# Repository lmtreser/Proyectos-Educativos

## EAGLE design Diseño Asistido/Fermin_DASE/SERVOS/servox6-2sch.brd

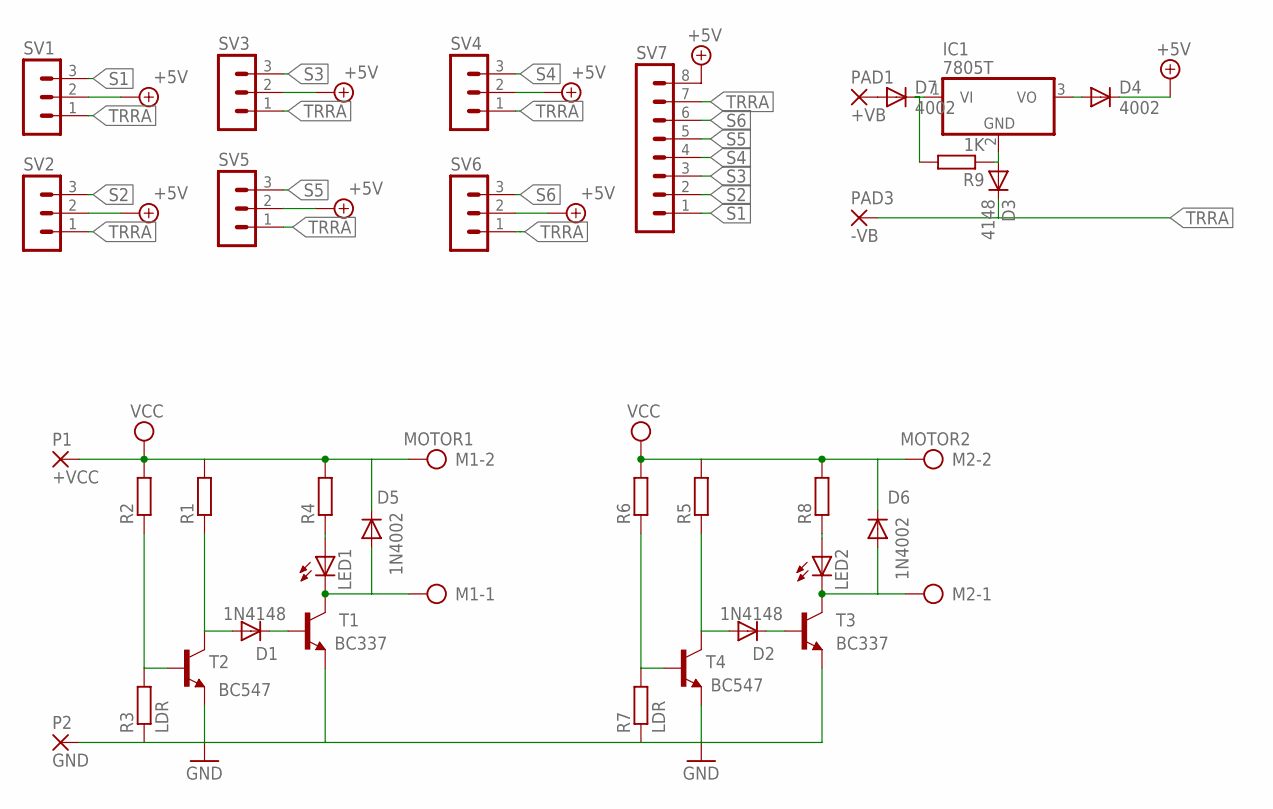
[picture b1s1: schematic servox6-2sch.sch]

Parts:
D1, D2: 1N4148; DO35-7
D3: 4148; DO35-7
D4, D7: 4002; DO35-7
D5, D6: 1N4002; DO41-10
IC1: 7805T; TO220H
LED1, LED2: LED3MM
M1: MOTOR1; AK500/2
M2: MOTOR2; AK500/2
P1: +VCC; 2,15/1,0
P2: GND; 2,15/1,0
PAD1: +VB; 1,6/0,9
PAD3: -VB; 1,6/0,9
R1, R2, R4, R5, R6, R8: R-EU_0207/7; 0207/7
R3, R7: LDR; 0204/5
R9: 1K; 0207/7
SV1, SV2, SV3, SV4, SV5, SV6: MA03-1
SV7: MA08-1
T1, T3: BC337; TO92-CBE
T2, T4: BC547; TO92-CBE

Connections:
+5V: D4.C, SV1.2, SV2.2, SV3.2, SV4.2, SV5.2, SV6.2, SV7.8
GND: P2.1, R3.1, R7.1, T1.E, T2.E, T3.E, T4.E
unnamed: D1.C, T1.B
unnamed: D1.A, R1.1, T2.C
unnamed: D5.A, LED1.K (C), M1.1, T1.C
unnamed: D3.A, IC1.2 (GND), R9.1
unnamed: LED1.A, R4.1
unnamed: R2.1, R3.2, T2.B
unnamed: D2.C, T3.B
unnamed: D2.A, R5.1, T4.C
unnamed: D6.A, LED2.K (C), M2.1, T3.C
unnamed: D4.A, IC1.3 (VO)
unnamed: R6.1, R7.2, T4.B
unnamed: LED2.A, R8.1
unnamed: D7.C, IC1.1 (VI), R9.2
unnamed: D7.A, PAD1.1
S1: SV1.3, SV7.1
S2: SV2.3, SV7.2
S3: SV3.3, SV7.3
S4: SV4.3, SV7.4
S5: SV5.3, SV7.5
S6: SV6.3, SV7.6
TRRA: D3.C, PAD3.1, SV1.1, SV2.1, SV3.1, SV4.1, SV5.1, SV6.1, SV7.7
VCC: D5.C, D6.C, M1.2, M2.2, P1.1, R1.2, R2.2, R4.2, R5.2, R6.2, R8.2

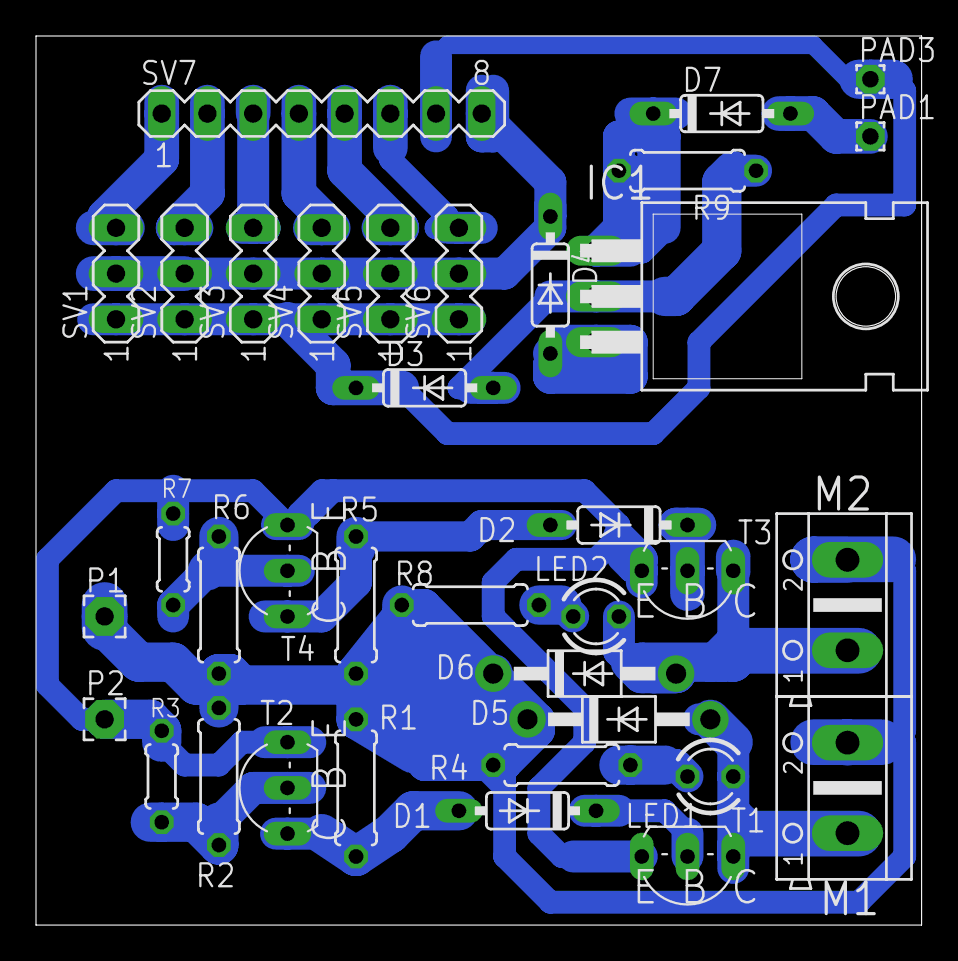
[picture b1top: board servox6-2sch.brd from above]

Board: 2 copper layers, 49.2 x 49.4 mm, 36 parts (0 on the bottom side), 24 nets.

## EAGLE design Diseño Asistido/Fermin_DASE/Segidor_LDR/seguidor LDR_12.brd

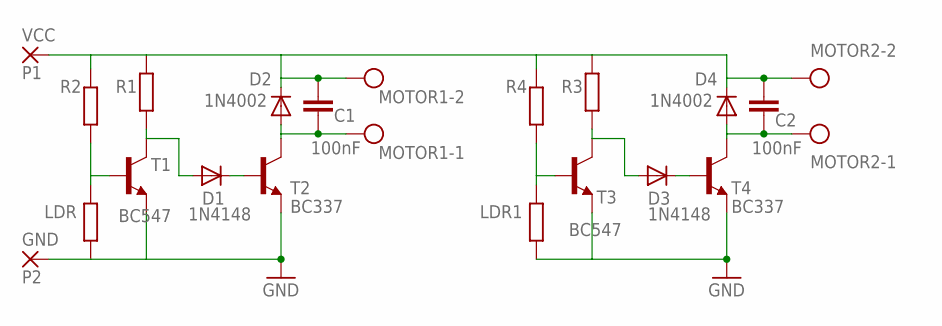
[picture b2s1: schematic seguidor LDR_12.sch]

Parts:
C1, C2: 100nF; C050-025X075
D1, D3: 1N4148; DO35-10
D2, D4: 1N4002; DO41-10
GND: P2; 2,15/1,0
LDR, LDR1: R-EU_0204/5; 0204/5
MOTOR1, MOTOR2: AK500/2
R1, R2, R3, R4: R-EU_0207/10; 0207/10
T1, T3: BC547; TO92-CBE
T2, T4: BC337; TO92-CBE
VCC: P1; 2,15/1,0

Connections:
GND: GND.1, LDR.1, LDR1.1, T1.E, T2.E, T3.E, T4.E
unnamed: LDR.2, R2.1, T1.B
unnamed: LDR1.2, R4.1, T3.B
unnamed: C1.1, C2.1, D2.C, D4.C, MOTOR1.2, MOTOR2.2, R1.2, R2.2, R3.2, R4.2, VCC.1
unnamed: D3.A, R3.1, T3.C
unnamed: D1.A, R1.1, T1.C
unnamed: D1.C, T2.B
unnamed: C1.2, D2.A, MOTOR1.1, T2.C
unnamed: D3.C, T4.B
unnamed: C2.2, D4.A, MOTOR2.1, T4.C

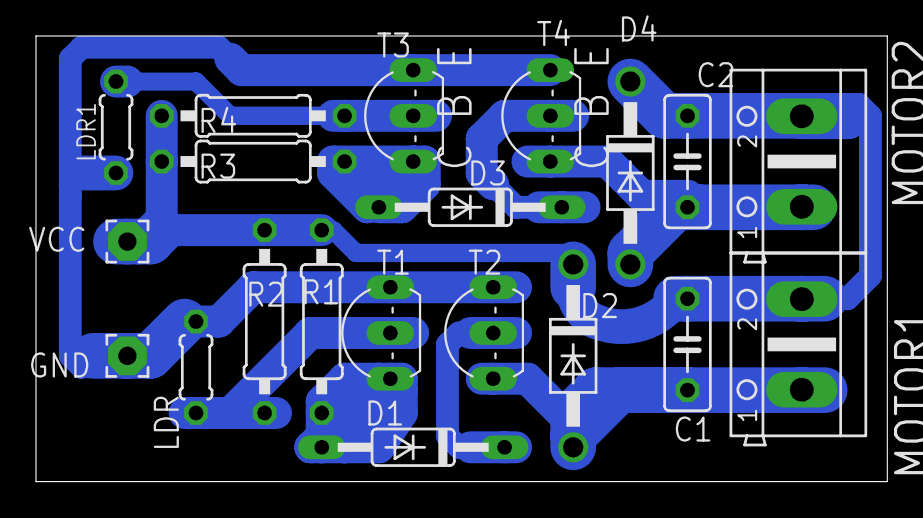
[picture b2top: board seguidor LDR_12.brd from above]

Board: 2 copper layers, 47.3 x 24.8 mm, 20 parts (0 on the bottom side), 10 nets.

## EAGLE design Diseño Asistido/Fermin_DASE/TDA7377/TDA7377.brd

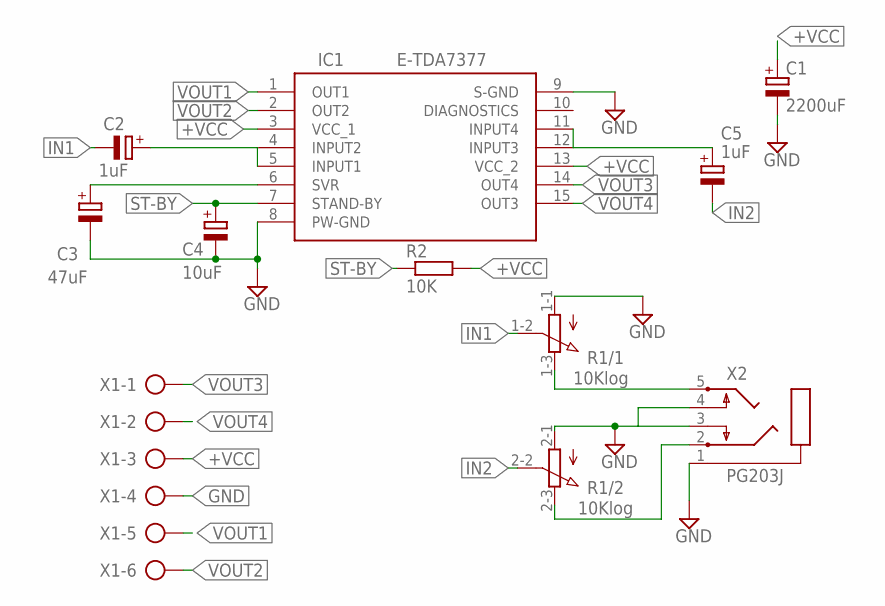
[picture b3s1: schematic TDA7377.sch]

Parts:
C1: 2200uF; E5-13
C2: 1uF; E2,5-6
C3: 47uF; E2,5-6
C4: 10uF; E2,5-5
C5: 1uF; E5-5
IC1: E-TDA7377; TO127P500X2020X2210-15P
R1: 10Klog; 3RP/1610G
R2: 10K; 0207/10
X1: AK500/6-H
X2: PG203J

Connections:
+VCC: C1.+, IC1.3 (VCC_1), IC1.13 (VCC_2), R2.2, X1.3
GND: C1.-, C3.-, C4.-, IC1.8 (PW-GND), IC1.9 (S-GND), R1.1-1 (A), R1.2-1 (A), X1.4, X2.1, X2.3, X2.4
IN1: C2.-, R1.1-2 (S)
IN2: C5.-, R1.2-2 (S)
unnamed: C2.+, IC1.4 (INPUT2), IC1.5 (INPUT1)
unnamed: C3.+, IC1.6 (SVR)
unnamed: C5.+, IC1.11 (INPUT4), IC1.12 (INPUT3)
unnamed: R1.2-3 (E), X2.2
unnamed: R1.1-3 (E), X2.5
ST-BY: C4.+, IC1.7 (STAND-BY), R2.1
VOUT1: IC1.1 (OUT1), X1.5
VOUT2: IC1.2 (OUT2), X1.6
VOUT3: IC1.14 (OUT4), X1.1
VOUT4: IC1.15 (OUT3), X1.2

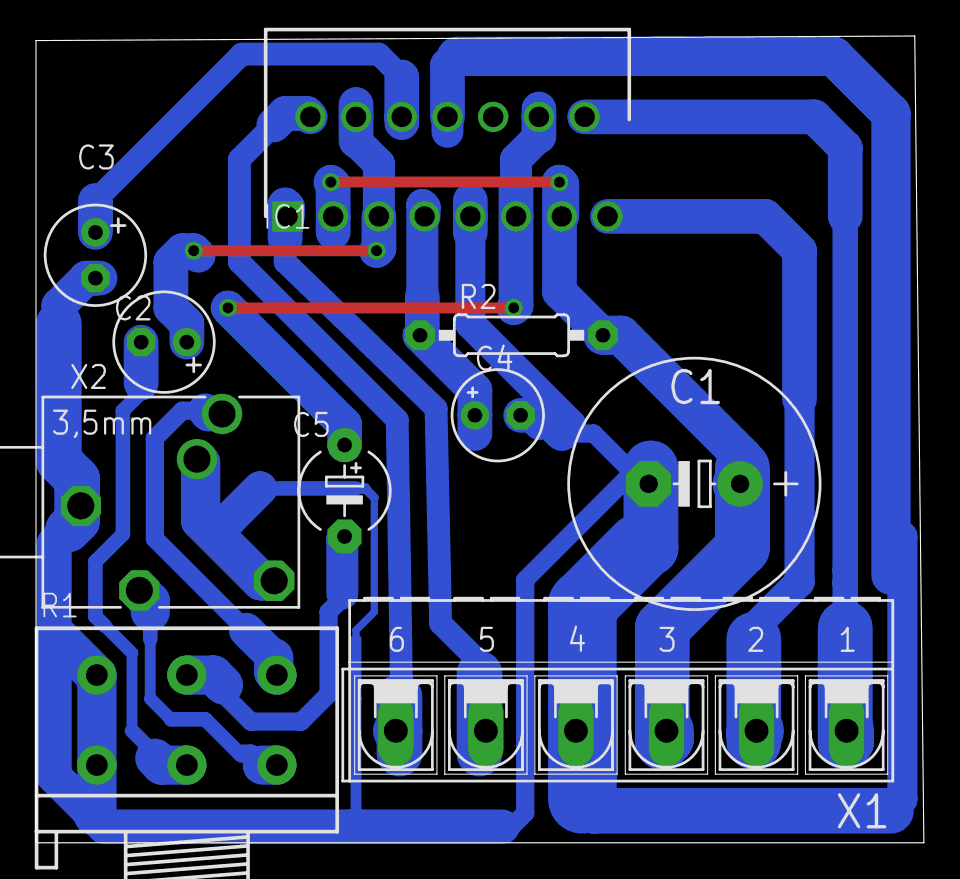
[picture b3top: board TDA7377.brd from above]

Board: 2 copper layers, 49.3 x 44.8 mm, 10 parts (0 on the bottom side), 14 nets.

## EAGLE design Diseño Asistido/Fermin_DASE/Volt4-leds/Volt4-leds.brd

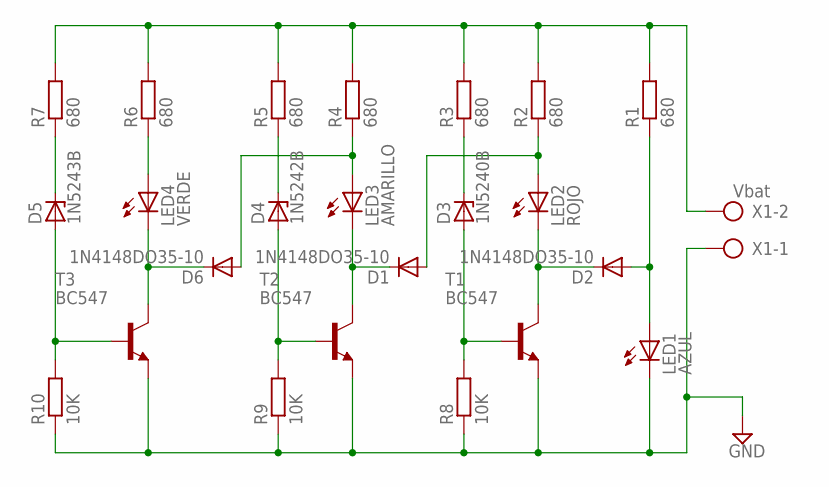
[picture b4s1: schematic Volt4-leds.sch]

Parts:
D1, D2, D6: 1N4148DO35-10; DO35-10
D3: 1N5240B; DO35Z10
D4: 1N5242B; DO35Z10
D5: 1N5243B; DO35Z10
LED1: AZUL; LED3MM
LED2: ROJO; LED3MM
LED3: AMARILLO; LED3MM
LED4: VERDE; LED3MM
R1, R2, R3, R4, R5, R6, R7: 680; 0207/10
R8, R9, R10: 10K; 0207/10
T1, T2, T3: BC547; TO92
X1: Vbat; AK500/2

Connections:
GND: LED1.K (C), R8.1, R9.1, R10.1, T1.1 (E), T2.1 (E), T3.1 (E), X1.1
unnamed: R1.2, R2.2, R3.2, R4.2, R5.2, R6.2, R7.2, X1.2
unnamed: D3.C, R3.1
unnamed: D1.A, LED2.A, R2.1
unnamed: D2.C, LED2.K (C), T1.3 (C)
unnamed: D3.A, R8.2, T1.2 (B)
unnamed: D5.A, R10.2, T3.2 (B)
unnamed: D4.A, R9.2, T2.2 (B)
unnamed: D1.C, LED3.K (C), T2.3 (C)
unnamed: D6.A, LED3.A, R4.1
unnamed: D4.C, R5.1
unnamed: D6.C, LED4.K (C), T3.3 (C)
unnamed: LED4.A, R6.1
unnamed: D5.C, R7.1
unnamed: D2.A, LED1.A, R1.1

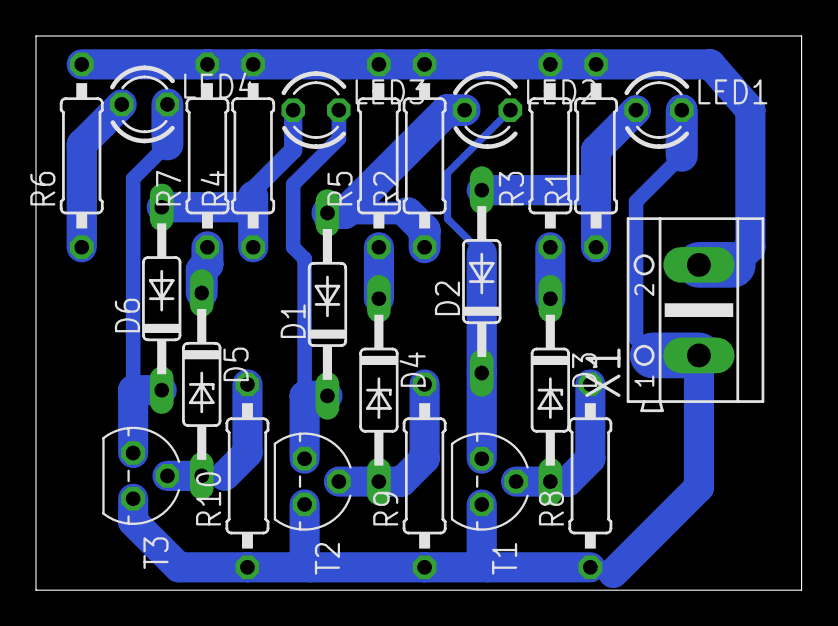
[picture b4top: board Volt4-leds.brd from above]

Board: 2 copper layers, 42.5 x 30.8 mm, 24 parts (0 on the bottom side), 15 nets.

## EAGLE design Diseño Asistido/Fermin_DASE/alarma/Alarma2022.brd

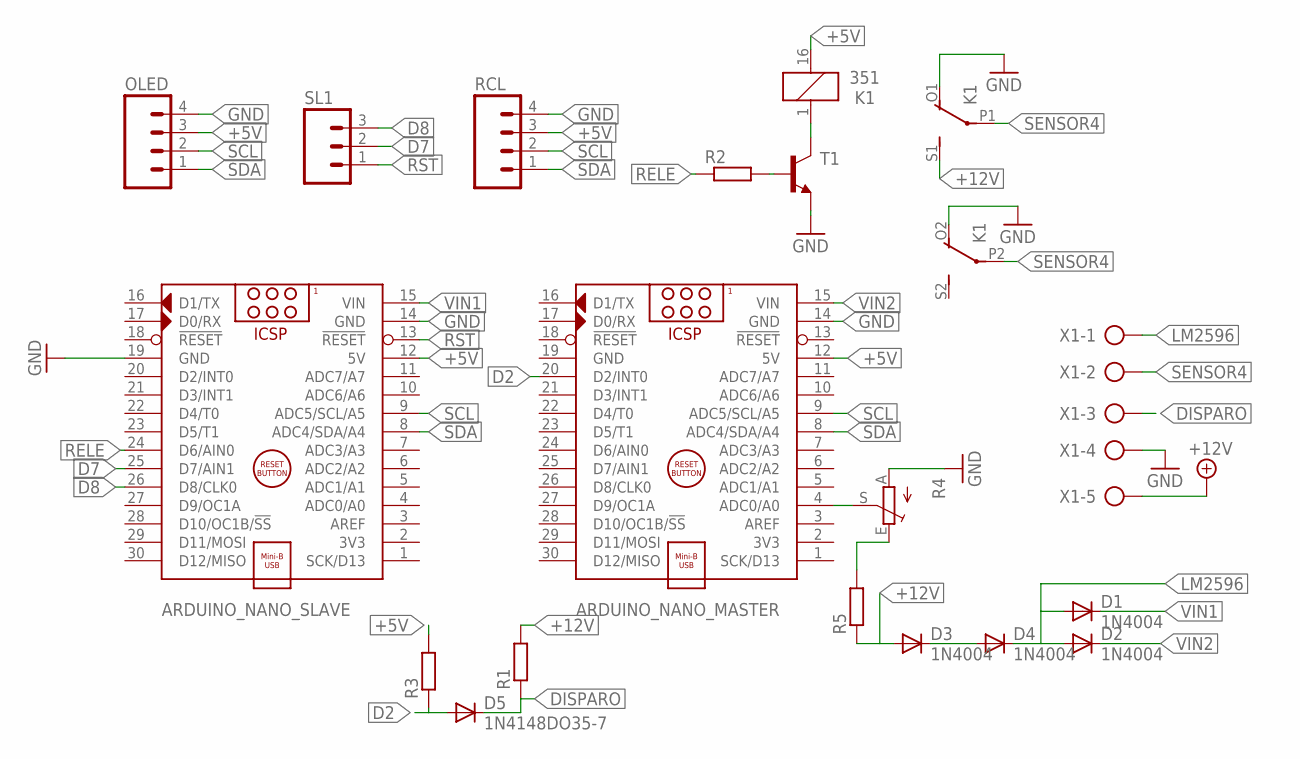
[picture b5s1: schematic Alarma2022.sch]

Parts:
ARDUINO_NANO_MASTER: ARDUINO_NANO
ARDUINO_NANO_SLAVE: ARDUINO_NANO
D1, D2, D3, D4: 1N4004; DO41-10
D5: 1N4148DO35-7; DO35-7
K1: 351
OLED: M04; 04P
R1, R2, R3: R-EU_0207/10; 0207/10
R4: TRIM_EU-B64Y; B64Y
R5: R-EU_0207/7; 0207/7
RCL: M04; 04P
SL1: M03; 03P
T1: BC337-NPN-TO92-CBE; TO92-CBE
X1: AK500/5-H

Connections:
+5V: ARDUINO_NANO_MASTER.12 (5V), ARDUINO_NANO_SLAVE.12 (5V), K1.16 (2), OLED.3, R3.2, RCL.3
+12V: D3.A, K1.S1 (S), R1.2, R5.1, X1.5
D2: ARDUINO_NANO_MASTER.20 (D2/INT0), D5.A, R3.1
D7: ARDUINO_NANO_SLAVE.25 (D7/AIN1), SL1.2
D8: ARDUINO_NANO_SLAVE.26 (D8/CLK0), SL1.3
DISPARO: D5.C, R1.1, X1.3
GND: ARDUINO_NANO_MASTER.14 (GND), ARDUINO_NANO_MASTER.19 (GND), ARDUINO_NANO_SLAVE.14 (GND), ARDUINO_NANO_SLAVE.19 (GND), K1.O1 (O), K1.O2 (O), OLED.4, R4.A, RCL.4, T1.E, X1.4
LM2596: D1.A, D2.A, D4.C, X1.1
unnamed: K1.1, T1.C
unnamed: R2.2, T1.B
unnamed: ARDUINO_NANO_MASTER.4 (ADC0/A0), R4.S
unnamed: R4.E, R5.2
unnamed: D3.C, D4.A
RELE: ARDUINO_NANO_SLAVE.24 (D6/AIN0), R2.1
RST: ARDUINO_NANO_SLAVE.13 (!RESET), SL1.1
SCL: ARDUINO_NANO_MASTER.9 (ADC5/SCL/A5), ARDUINO_NANO_SLAVE.9 (ADC5/SCL/A5), OLED.2, RCL.2
SDA: ARDUINO_NANO_MASTER.8 (ADC4/SDA/A4), ARDUINO_NANO_SLAVE.8 (ADC4/SDA/A4), OLED.1, RCL.1
SENSOR4: K1.P1, K1.P2, X1.2
VIN1: ARDUINO_NANO_SLAVE.15 (VIN), D1.C
VIN2: ARDUINO_NANO_MASTER.15 (VIN), D2.C

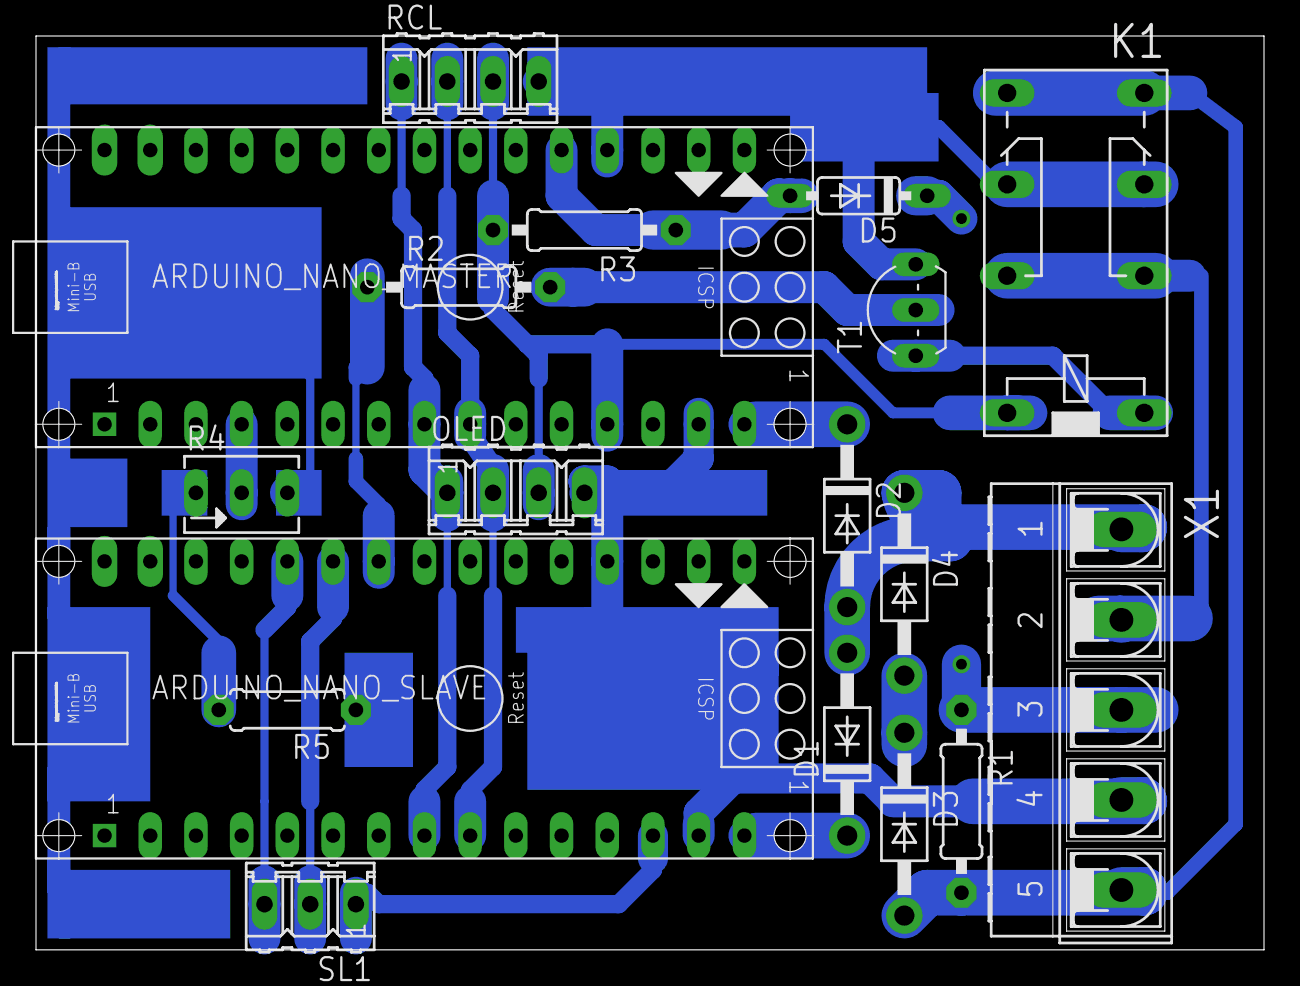
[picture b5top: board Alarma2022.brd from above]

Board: 2 copper layers, 68.2 x 50.8 mm, 18 parts (0 on the bottom side), 20 nets.

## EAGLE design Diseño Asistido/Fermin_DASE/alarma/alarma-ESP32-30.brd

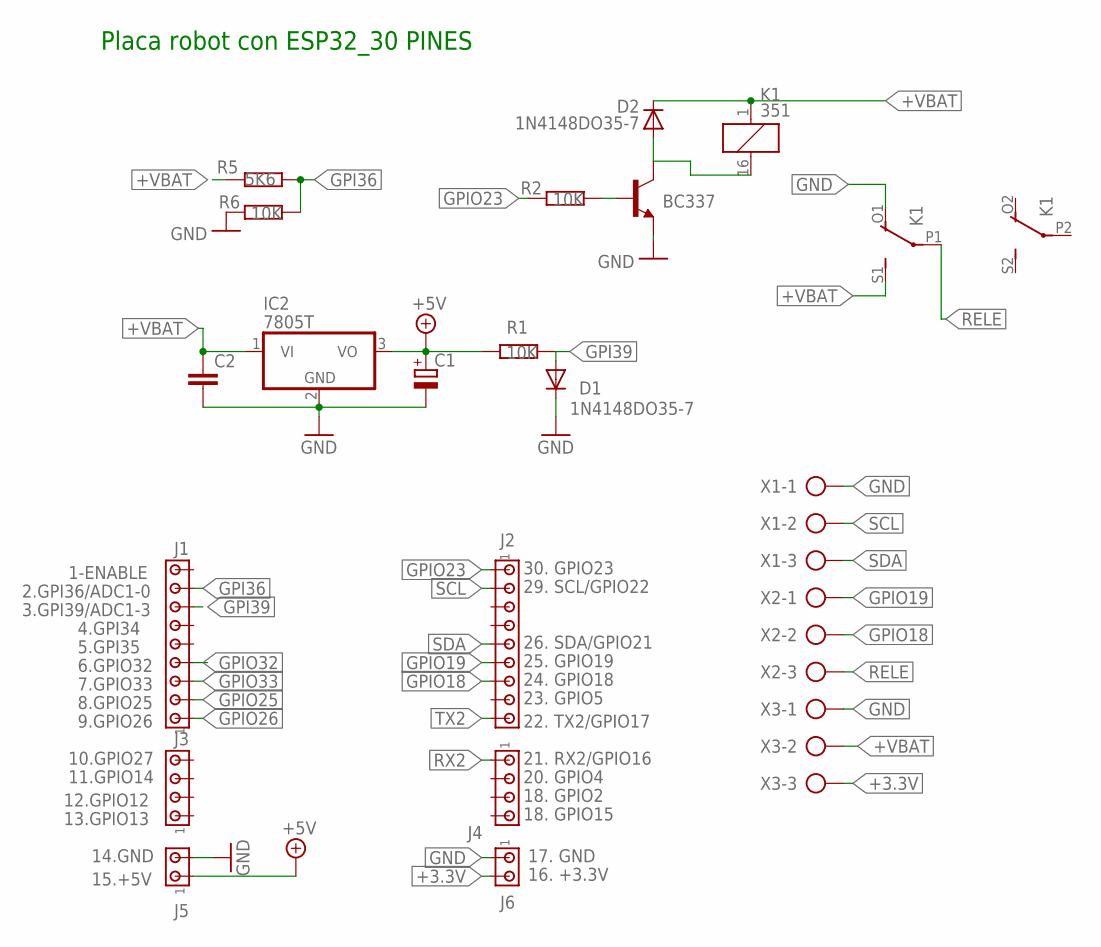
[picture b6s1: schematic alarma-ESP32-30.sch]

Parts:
BC337: BC337-16-NPN-TO92-CBE; TO92-CBE
C1: CPOL-EUE2.5-6; E2,5-6
C2: C-EU025-025X050; C025-025X050
D1, D2: 1N4148DO35-7; DO35-7
IC2: 7805T; TO220H
J1, J2: MTA09-100; 10X09MTA
J3, J4: MTA04-100; 10X04MTA
J5, J6: MTA02-100; 10X02MTA
K1: 351
R1, R6: 10K; 0207/7
R2: 10K; 0207/15
R5: 5K6; 0207/7
X1, X2, X3: AK500/3

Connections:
+3.3V: J6.2, X3.3
+5V: C1.+, IC2.3 (VO), J5.1, R1.2
+VBAT: C2.1, D2.C, IC2.1 (VI), K1.1, K1.S1 (S), R5.1, X3.2
GND: BC337.E, C1.-, C2.2, D1.C, IC2.2 (GND), J5.2, J6.1, K1.O1 (O), R6.2, X1.1, X3.1
GPI36: J1.8, R5.2, R6.1
GPI39: D1.A, J1.7, R1.1
GPIO18: J2.7, X2.2
GPIO19: J2.6, X2.1
GPIO23: J2.1, R2.2
GPIO25: J1.2
GPIO26: J1.1
GPIO32: J1.4
GPIO33: J1.3
unnamed: BC337.C, D2.A, K1.16 (2)
unnamed: BC337.B, R2.1
RELE: K1.P1, X2.3
RX2: J4.1
SCL: J2.2, X1.2
SDA: J2.5, X1.3
TX2: J2.9

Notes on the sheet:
16. +3.3V
1-ENABLE
2.GPI36/ADC1-0
3.GPI39/ADC1-3
4.GPI34
5.GPI35
6.GPIO32
7.GPIO33
8.GPIO25
9.GPIO26
10.GPIO27
11.GPIO14
13.GPIO13
15.+5V
30. GPIO23
29. SCL/GPIO22
26. SDA/GPIO21
14.GND
25. GPIO19
24. GPIO18
22. TX2/GPIO17
21. RX2/GPIO16
20. GPIO4
Placa robot con ESP32_30 PINES
12.GPIO12
17. GND
18. GPIO15
18. GPIO2
23. GPIO5

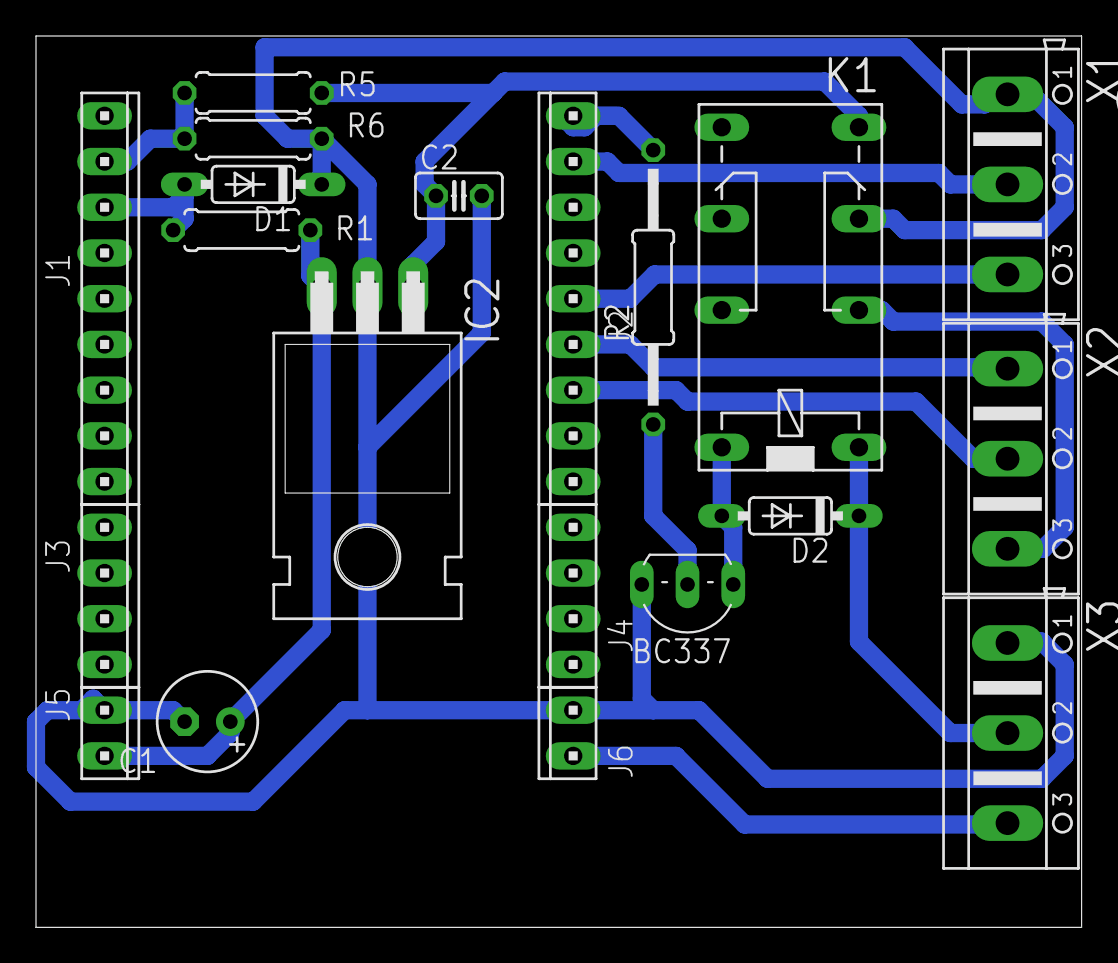
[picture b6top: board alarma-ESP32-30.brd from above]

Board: 2 copper layers, 58.1 x 49.5 mm, 20 parts (0 on the bottom side), 14 nets.

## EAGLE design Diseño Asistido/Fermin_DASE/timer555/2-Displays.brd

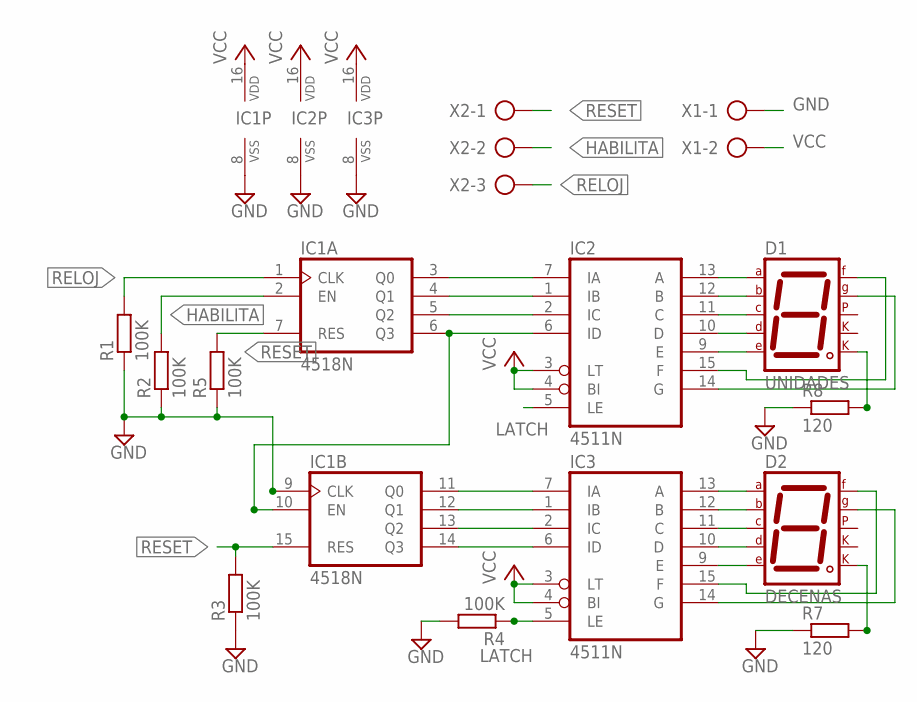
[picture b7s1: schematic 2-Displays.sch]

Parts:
D1: UNIDADES; 7SEG-13
D2: DECENAS; 7SEG-13
IC1: 4518N; DIL16
IC2, IC3: 4511N; DIL16
R1, R2, R3, R4, R5: 100K; 0207/7
R7, R8: 120; 0207/7
X1: AK500/2-H
X2: AK500/3-H

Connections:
GND: IC1.8 (VSS), IC1.9 (CLK), IC2.8 (VSS), IC3.8 (VSS), R1.1, R2.1, R3.1, R4.2, R5.1, R7.1, R8.1, X1.1
HABILITA: IC1.2 (EN), R2.2, X2.2
LATCH: IC2.5 (LE), IC3.5 (LE), R4.1
unnamed: IC1.3 (Q0), IC2.7 (IA)
unnamed: IC1.4 (Q1), IC2.1 (IB)
unnamed: IC1.5 (Q2), IC2.2 (IC)
unnamed: D1.8 (CK2), R8.2
unnamed: D2.7 (A), IC3.13 (A)
unnamed: D2.6 (B), IC3.12 (B)
unnamed: D2.4 (C), IC3.11 (C)
unnamed: D2.2 (D), IC3.10 (D)
unnamed: D2.1 (E), IC3.9 (E)
unnamed: IC1.11 (Q0), IC3.7 (IA)
unnamed: IC1.12 (Q1), IC3.1 (IB)
unnamed: IC1.14 (Q3), IC3.6 (ID)
unnamed: IC1.13 (Q2), IC3.2 (IC)
unnamed: D2.9 (F), IC3.15 (F)
unnamed: D2.10 (G), IC3.14 (G)
unnamed: D2.8 (CK2), R7.2
unnamed: D1.7 (A), IC2.13 (A)
unnamed: D1.6 (B), IC2.12 (B)
unnamed: D1.4 (C), IC2.11 (C)
unnamed: D1.2 (D), IC2.10 (D)
unnamed: D1.1 (E), IC2.9 (E)
unnamed: D1.9 (F), IC2.15 (F)
unnamed: D1.10 (G), IC2.14 (G)
unnamed: IC1.6 (Q3), IC1.10 (EN), IC2.6 (ID)
RELOJ: IC1.1 (CLK), R1.2, X2.3
RESET: IC1.7 (RES), IC1.15 (RES), R3.2, R5.2, X2.1
VCC: IC1.16 (VDD), IC2.3 (LT), IC2.4 (BI), IC2.16 (VDD), IC3.3 (LT), IC3.4 (BI), IC3.16 (VDD), X1.2

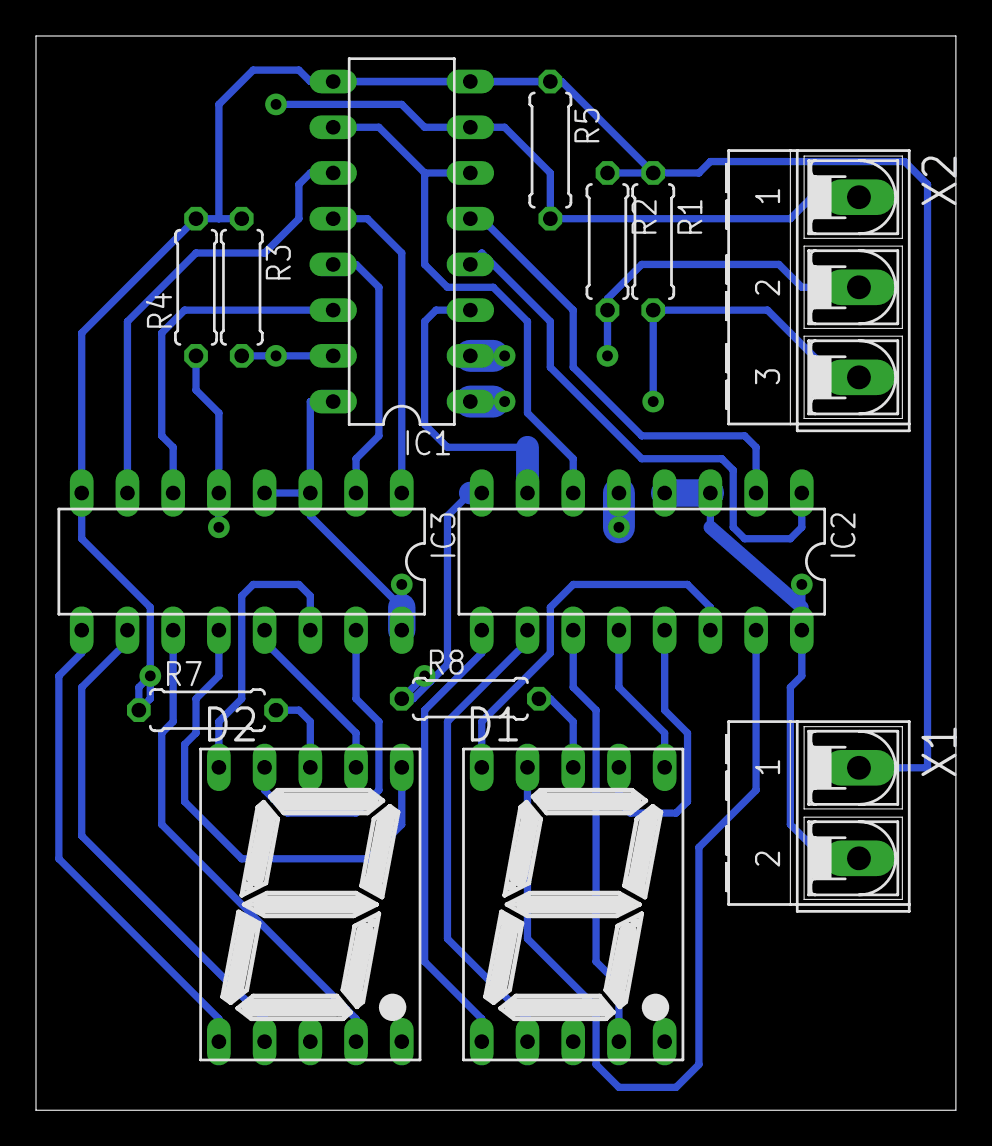
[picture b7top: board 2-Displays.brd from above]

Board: 2 copper layers, 51.1 x 59.7 mm, 14 parts (0 on the bottom side), 30 nets.
